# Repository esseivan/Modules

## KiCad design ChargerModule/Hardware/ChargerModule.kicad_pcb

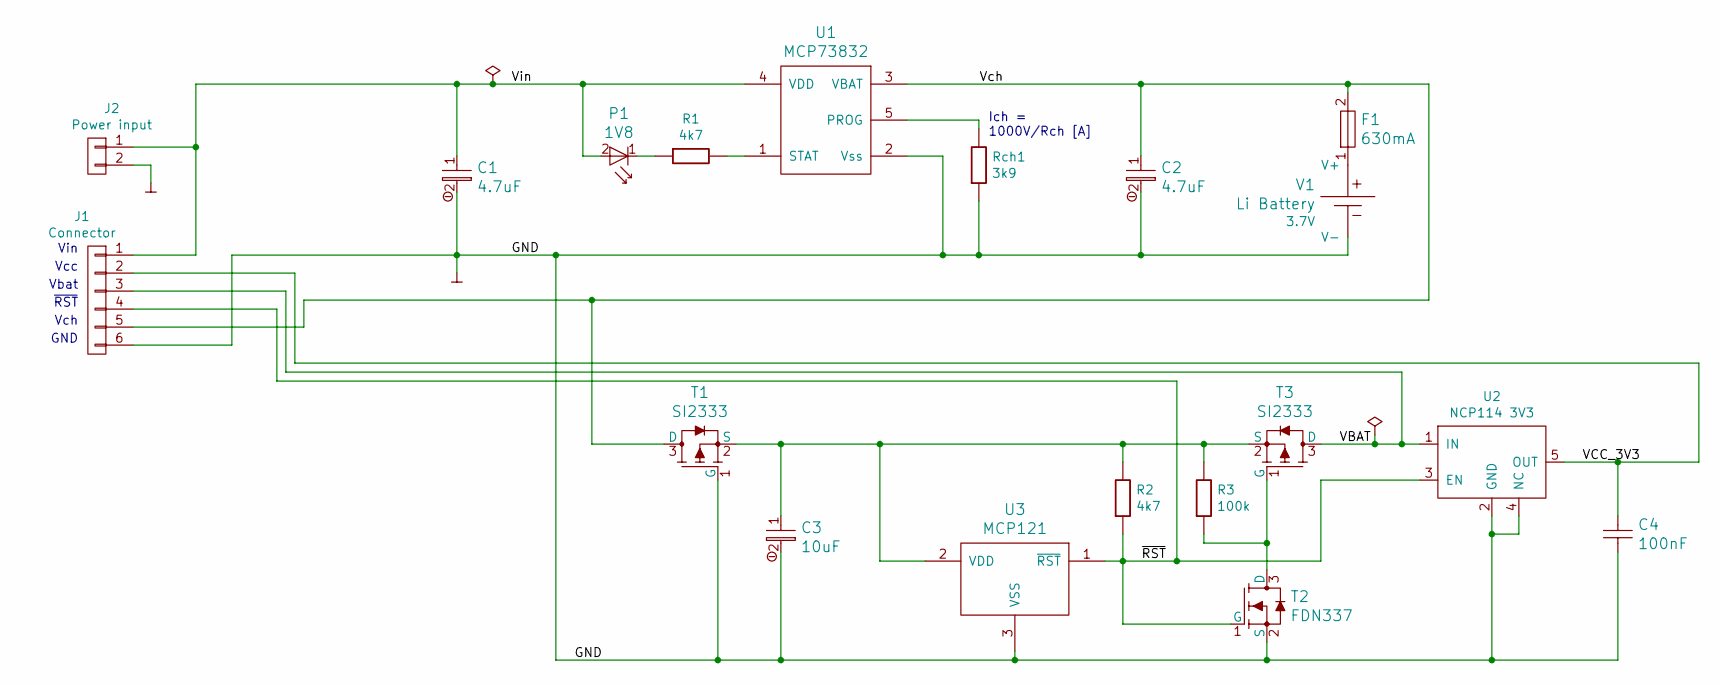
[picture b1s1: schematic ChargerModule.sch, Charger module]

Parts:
C1, C2: 4.7uF; C_1206_HandSoldering
C3: 10uF; C_0805_HandSoldering
C4: 100nF; C_0805_HandSoldering
F1: 630mA; Fuse_SMD1206_HandSoldering
J1: Connector; MicroMatch_6P_Male
J2: Power input; WireConn_02
P1: 1V8; D_0603_HandSoldering
R1, R2: 4k7; R_0603_HandSoldering
R3: 100k; R_0805_HandSoldering
Rch1: 3k9; R_0603_HandSoldering
T1, T3: SI2333; SOT-23_Handsoldering
T2: FDN337; SOT-23_Handsoldering
U1: MCP73832; SOT-23-5_HandSoldering
U2: NCP114 3V3; SOT-23-5_HandSoldering
U3: MCP121; SOT-23_Handsoldering
V1: Li Battery; 18650_Battery_holder; Voltage 3.7V

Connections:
/VBAT: J1.3, T3.3 (D), U2.1 (IN)
/VCC_3V3: C4.1, J1.2, U2.5 (OUT)
/Vch: C2.1, F1.2, J1.5, T1.3 (D), U1.3 (VBAT)
/Vin: C1.1, J1.1, J2.1, P1.2 (Anode), U1.4 (VDD)
/~RST: J1.4, R2.2, T2.1 (G), U2.3 (EN), U3.1 (~RST)
GND: C1.2, C2.2, C3.2, C4.2, J1.6, J2.2, Rch1.2, T1.1 (G), T2.2 (S), U1.2 (Vss), U2.2 (GND), U2.4 (NC), U3.3 (VSS), V1.2 (V-)
unnamed: C3.1, R2.1, R3.1, T1.2 (S), T3.2 (S), U3.2 (VDD)
unnamed: F1.1, V1.1 (V+)
unnamed: P1.1 (Cathode), R1.2
unnamed: R1.1, U1.1 (STAT)
unnamed: R3.2, T2.3 (D), T3.1 (G)
unnamed: Rch1.1, U1.5 (PROG)

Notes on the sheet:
Ich = 1000V/Rch [A]
Vin
GND
Vch
~RST
Vbat
Vcc

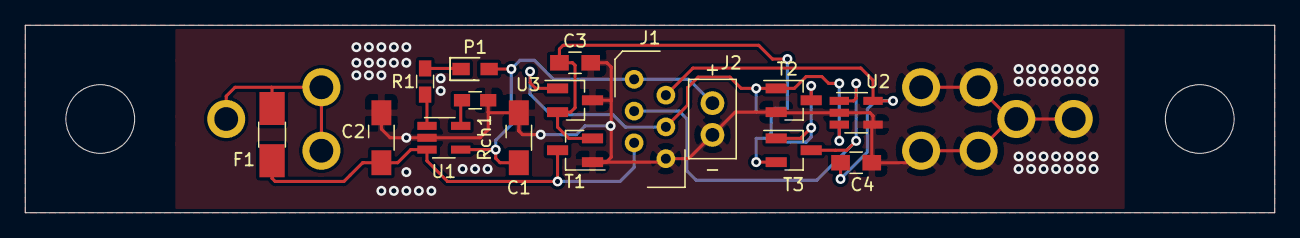
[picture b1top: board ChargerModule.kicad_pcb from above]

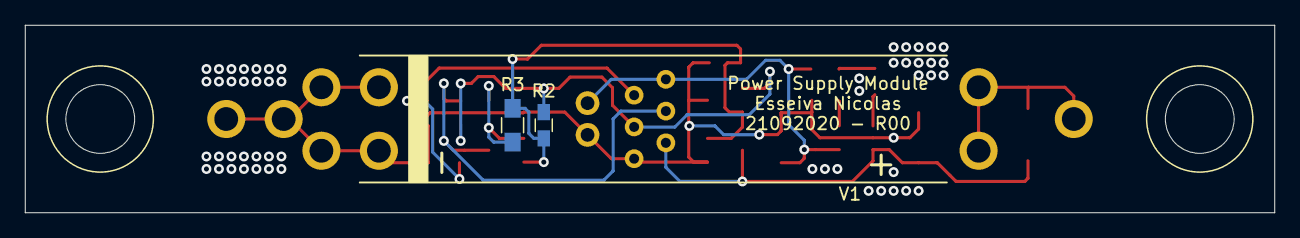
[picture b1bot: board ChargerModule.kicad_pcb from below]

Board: 2 copper layers, 100.0 x 15.0 mm, 20 parts (4 on the bottom side), 12 nets.

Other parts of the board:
VIS_M3_88mm_space: VIS_M5_88mm

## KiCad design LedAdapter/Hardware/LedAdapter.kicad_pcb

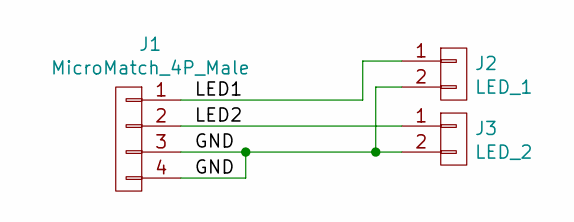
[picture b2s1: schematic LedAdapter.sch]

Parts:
J1: MicroMatch_4P_Male
J2: LED_1; WireConn_02
J3: LED_2; WireConn_02

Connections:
/GND: J1.3, J1.4, J2.2, J3.2
/LED1: J1.1, J2.1
/LED2: J1.2, J3.1

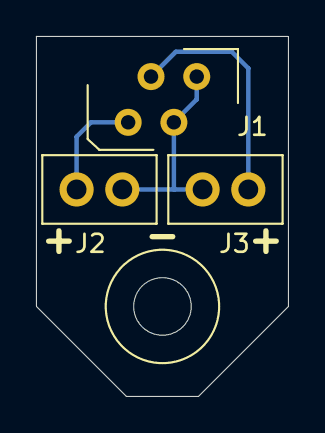
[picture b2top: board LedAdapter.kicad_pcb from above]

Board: 2 copper layers, 14.0 x 20.0 mm, 4 parts (0 on the bottom side), 3 nets.

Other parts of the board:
VIS_M5_space: VIS_M3

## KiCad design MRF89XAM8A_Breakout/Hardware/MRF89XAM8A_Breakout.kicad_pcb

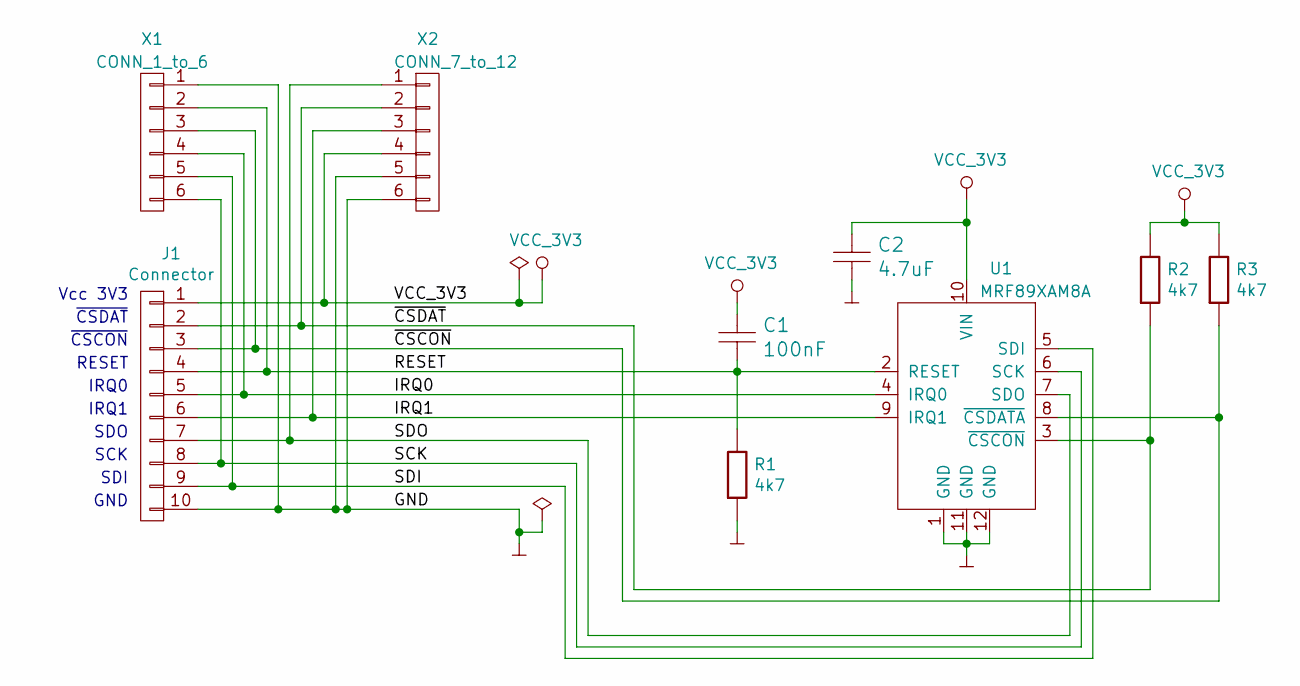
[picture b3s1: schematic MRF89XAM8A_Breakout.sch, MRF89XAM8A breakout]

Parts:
C1: 100nF; C_0805_HandSoldering
C2: 4.7uF; C_0805_HandSoldering
J1: Connector; MicroMatch_10P_Male
R1, R2, R3: 4k7; R_0805_HandSoldering
U1: MRF89XAM8A
X1: CONN_1_to_6; Pin_Header_Straight_1x06_Pitch2.54mm
X2: CONN_7_to_12; Pin_Header_Straight_1x06_Pitch2.54mm

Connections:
/IRQ0: J1.5, U1.4 (IRQ0), X1.4
/IRQ1: J1.6, U1.9 (IRQ1), X2.3
/RESET: C1.2, J1.4, R1.1, U1.2 (RESET), X1.2
/SCK: J1.8, U1.6 (SCK), X1.6
/SDI: J1.9, U1.5 (SDI), X1.5
/SDO: J1.7, U1.7 (SDO), X2.1
/~CSCON: J1.3, R3.2, U1.8 (~CSDATA), X1.3
/~CSDAT: J1.2, R2.2, U1.3 (~CSCON), X2.2
GND: C2.2, J1.10, R1.2, U1.1 (GND), U1.11 (GND), U1.12 (GND), X1.1, X2.5, X2.6
VCC_3V3: C1.1, C2.1, J1.1, R2.1, R3.1, U1.10 (VIN), X2.4

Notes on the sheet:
Vcc 3V3
GND
IRQ1
IRQ0
RESET
~CSCON
~CSDAT
SDO
SCK
SDI

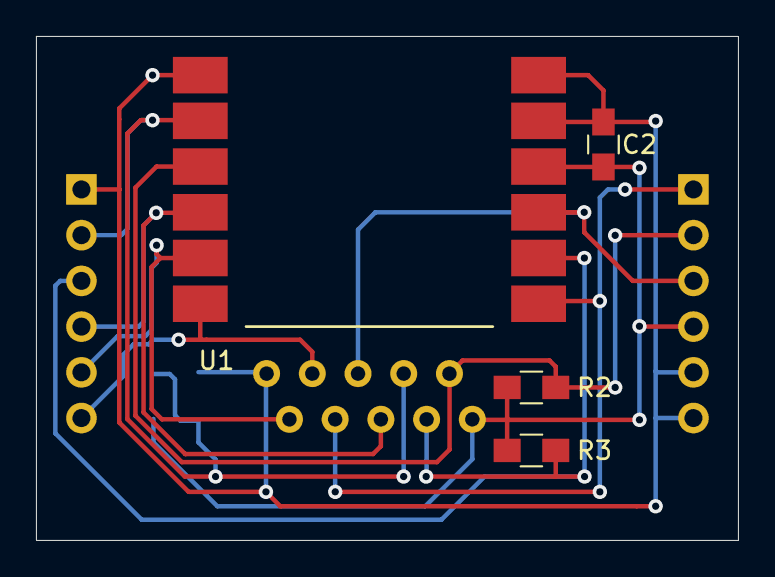
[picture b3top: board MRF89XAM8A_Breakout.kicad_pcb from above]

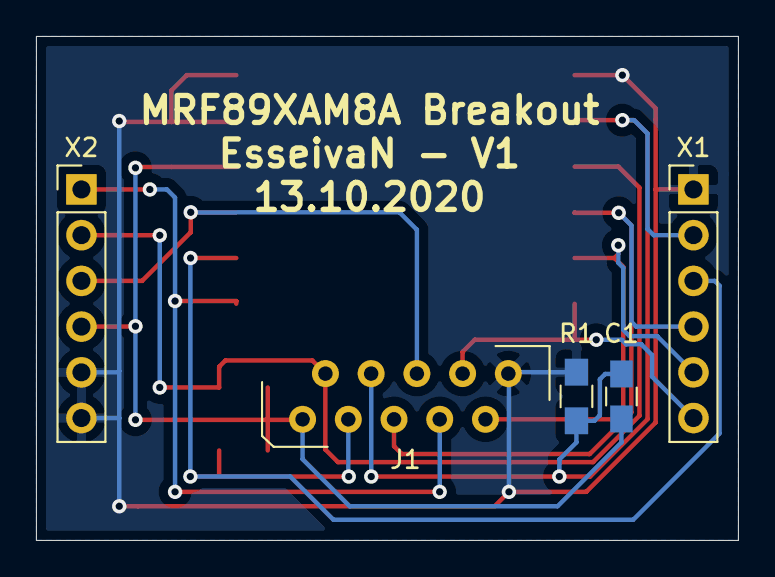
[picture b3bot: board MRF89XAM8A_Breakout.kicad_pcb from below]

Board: 2 copper layers, 39.0 x 28.0 mm, 9 parts (5 on the bottom side), 10 nets.

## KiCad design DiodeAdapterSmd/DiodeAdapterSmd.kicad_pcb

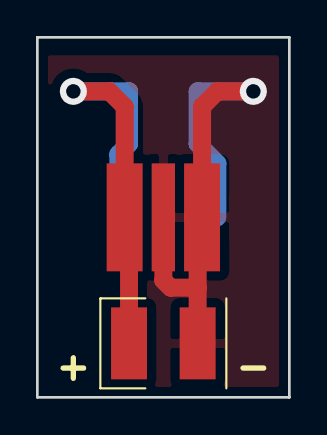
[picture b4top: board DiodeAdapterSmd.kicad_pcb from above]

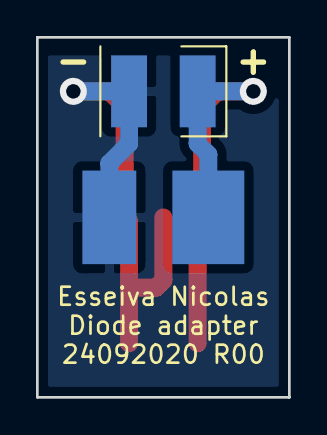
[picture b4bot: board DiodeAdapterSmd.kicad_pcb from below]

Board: 2 copper layers, 14.0 x 20.0 mm, 4 parts (2 on the bottom side), 2 nets.

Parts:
P1: LED; LED_LH351D
P2: LED; LED_LITTLE_STAR
X1, X2: CONN_01X02; WirePad_02

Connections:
/GND_1: P1.1, P2.1, X1.2, X2.2
/V+_1: P1.2, P2.2, X1.1, X2.1

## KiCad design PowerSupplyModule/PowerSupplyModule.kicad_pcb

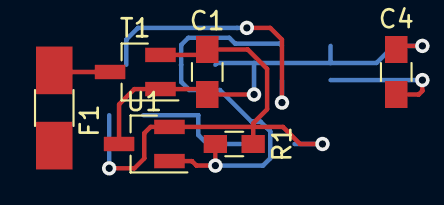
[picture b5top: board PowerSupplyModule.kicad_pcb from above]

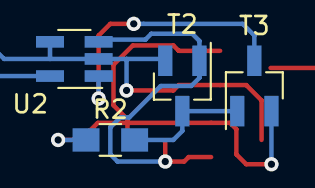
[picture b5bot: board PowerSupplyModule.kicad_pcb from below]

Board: 2 copper layers, 10 parts (4 on the bottom side), 7 nets.

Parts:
C1: 10uF; C_0805_HandSoldering
C4: 100nF; C_0805_HandSoldering
F1: 630mA; Fuse_SMD1206_HandSoldering
R1: 4k7; R_0603_HandSoldering
R2: 100k; R_0805_HandSoldering
T1, T3: SI2333; SOT-23_Handsoldering
T2: FDN337; SOT-23_Handsoldering
U1: MCP121; SOT-23_Handsoldering
U2: NCP114 3V3; SOT-23-5_HandSoldering

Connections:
/VBAT: T3.3, U2.1
/VCC_3V3: C4.1, U2.5
/~RST: R1.2, T2.1, U1.1, U2.3
GND_ALIM: C1.2, C4.2, T1.1, T2.2, U1.3, U2.2, U2.4
unnamed: C1.1, R1.1, R2.1, T1.2, T3.2, U1.2
unnamed: F1.2, T1.3
unnamed: R2.2, T2.3, T3.1

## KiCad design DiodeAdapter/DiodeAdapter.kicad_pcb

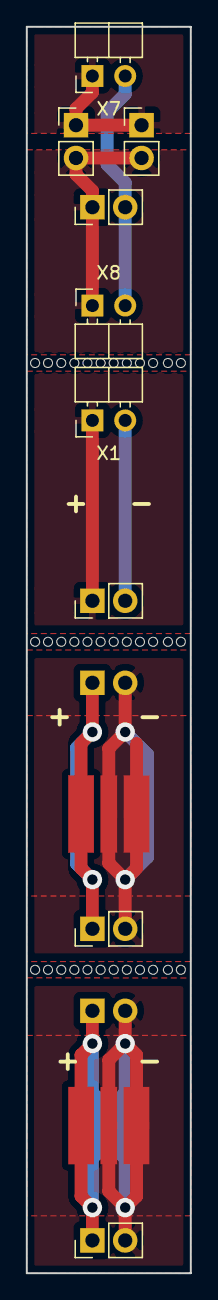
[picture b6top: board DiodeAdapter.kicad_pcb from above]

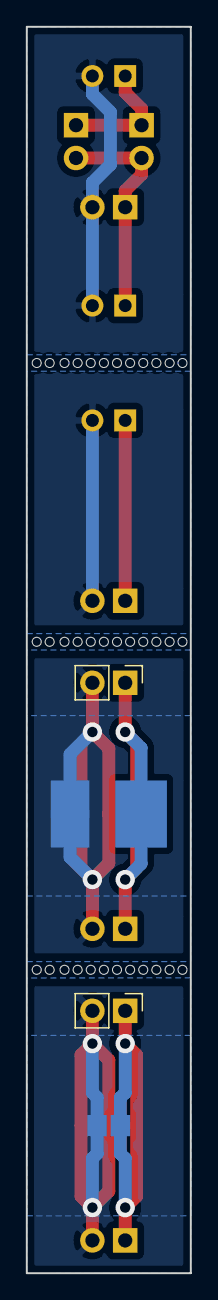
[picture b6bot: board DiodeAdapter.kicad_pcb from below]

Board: 2 copper layers, 12.7 x 96.5 mm, 15 parts (4 on the bottom side), 9 nets.

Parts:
P1, P3: LED; LED_LH351D
P2: LED; LED_LITTLE_STAR
P4: LED; LED_XQ_D
W1, W2: TEST_2P; Pin_Header_Straight_1x02_Pitch2.54mm
X1, X7: CONN_01X02; Pin_Header_Angled_1x02_Pitch2.54mm
X2, X3, X4, X5, X6, X9: CONN_01X02; Pin_Header_Straight_1x02_Pitch2.54mm
X8: CONN_01X02; Pin_Header_Angled_1x02_Pitch2.54mm_reverse

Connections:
/GND: X1.2, X2.2
/GND_1: P1.1, P2.1, X3.2, X4.2
/GND_2: P3.1, P4.1, X5.2, X6.2
/V+: X1.1, X2.1
/V+_1: P1.2, P2.2, X3.1, X4.1
/V+_2: P3.2, P4.2, X5.1, X6.1
unnamed: W1.1, W2.1, X7.1
unnamed: W1.2, W2.2, X8.1, X9.1
unnamed: X7.2, X8.2, X9.2

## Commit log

2020-09-21 create gerber zip
2020-09-28 Modifications
